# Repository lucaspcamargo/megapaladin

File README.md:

# mega-paladin v3 (WIP)

This is a switchless region mod for the SEGA Mega Drive, and a bluetooth controller host and adapter, based on the Raspberry Pi Pico W.

For now the mod is quite simple, allowing to change the region of the console via a reset button bypass.
Hold reset for half a second and release, to change desired region. The power LED will blink once for US, twice for EU, and three times for JP. Then do a quick press of the reset button to apply the setting and reset the console. Easy peasy.

Since this mod maintains the original power LED and communicates the region setting via blinking, there's no need to change anything about the external appearance of the console. It should look exactly the same after installation.

WIP WIP WIP :: Wireless controller functionality is coming along, when using a Pico W. [Bluepad32](https://github.com/ricardoquesada/bluepad32) is working well as the joystick host solution, and it supports a wide variety of controllers.

PIO for proper controller port interfacing is on the way.

For more info on this mod, and the thought process, check out TODO, and maybe also [this post](https://camargo.eng.br/blog/2023/11-18-pal-megadrive.html) for the first version.

## Building

Install dependencies for `pico-sdk`. They were `cmake gcc-arm-none-eabi libnewlib-arm-none-eabi build-essential` at time of writing (on Arch).

```
$ git submodule update --init --recursive   # pico-sdk pulls in a lot of submodules, it's ok though
$ mkdir build && cd build
$ cmake ..
$ make
```

`megapaladin.uf2` should be in the `build` folder, ready to be flashed.

## Flashing

For the first flashing, proceed as if flashing any other Pico W device via UF2. Namely:

+ use uf2 file for initial installation
+ plug usb cable in computer keeping BOOTSEL button held
+ copy uf2 file into the disk device that appears
+ umount disk

Further flashing of modified firmware after initial setup can be done with:

```sh
picotool load -f -x build/megapaladin.elf
```

`picotool` may have to be installed separately.

Use `sudo` if there are permission errors reported (most likely missing `udev` rules, if on Linux). Check the `pico-sdk` and/or the `picotool` documentation for more info.

## Hardware Installation

An installation diagram is provided [here](doc/install%20plan.png). **(It needs updating for V3!)** It is for VA 6.5, check out other switchless mod install guides for other revisions/models.

## Warnings

### Connect the USB cable only when the Mega Drive is on

The 5V supply side should be protected from reverse-feeding the console via a diode. Also, the level shifters should maintain a high-impedance state on the 5V side when the console is off.

This was tested a couple of times. I cannot guarantee this behavior, though! Weird leakage could happen, potentially damaging your console. 

You have been warned.

## License

This project is licensed under the GPL v3. See the [LICENSE](LICENSE) file for more information.

## Troubleshooting

If you encounter issues with region switching or controller connectivity, try the following steps:

- Ensure that the reset button is being properly bypassed, and that the reset button output is cut off from feeding the IO controller's reset line.
- Double-check all wiring and solder joints.
- Ensure the Pico W is properly flashed and powered.
- Verify the reset button timing as described in the usage section.
- Consult the [Bluepad32 documentation](https://github.com/ricardoquesada/bluepad32) for controller pairing issues.

## Contributing

Contributions are welcome! Please open issues or submit pull requests for bug fixes, improvements, or new features.

## Contact

For questions or feedback, [open an issue on GitHub](https://github.com/lucaspcamargo/megapaladin/issues).

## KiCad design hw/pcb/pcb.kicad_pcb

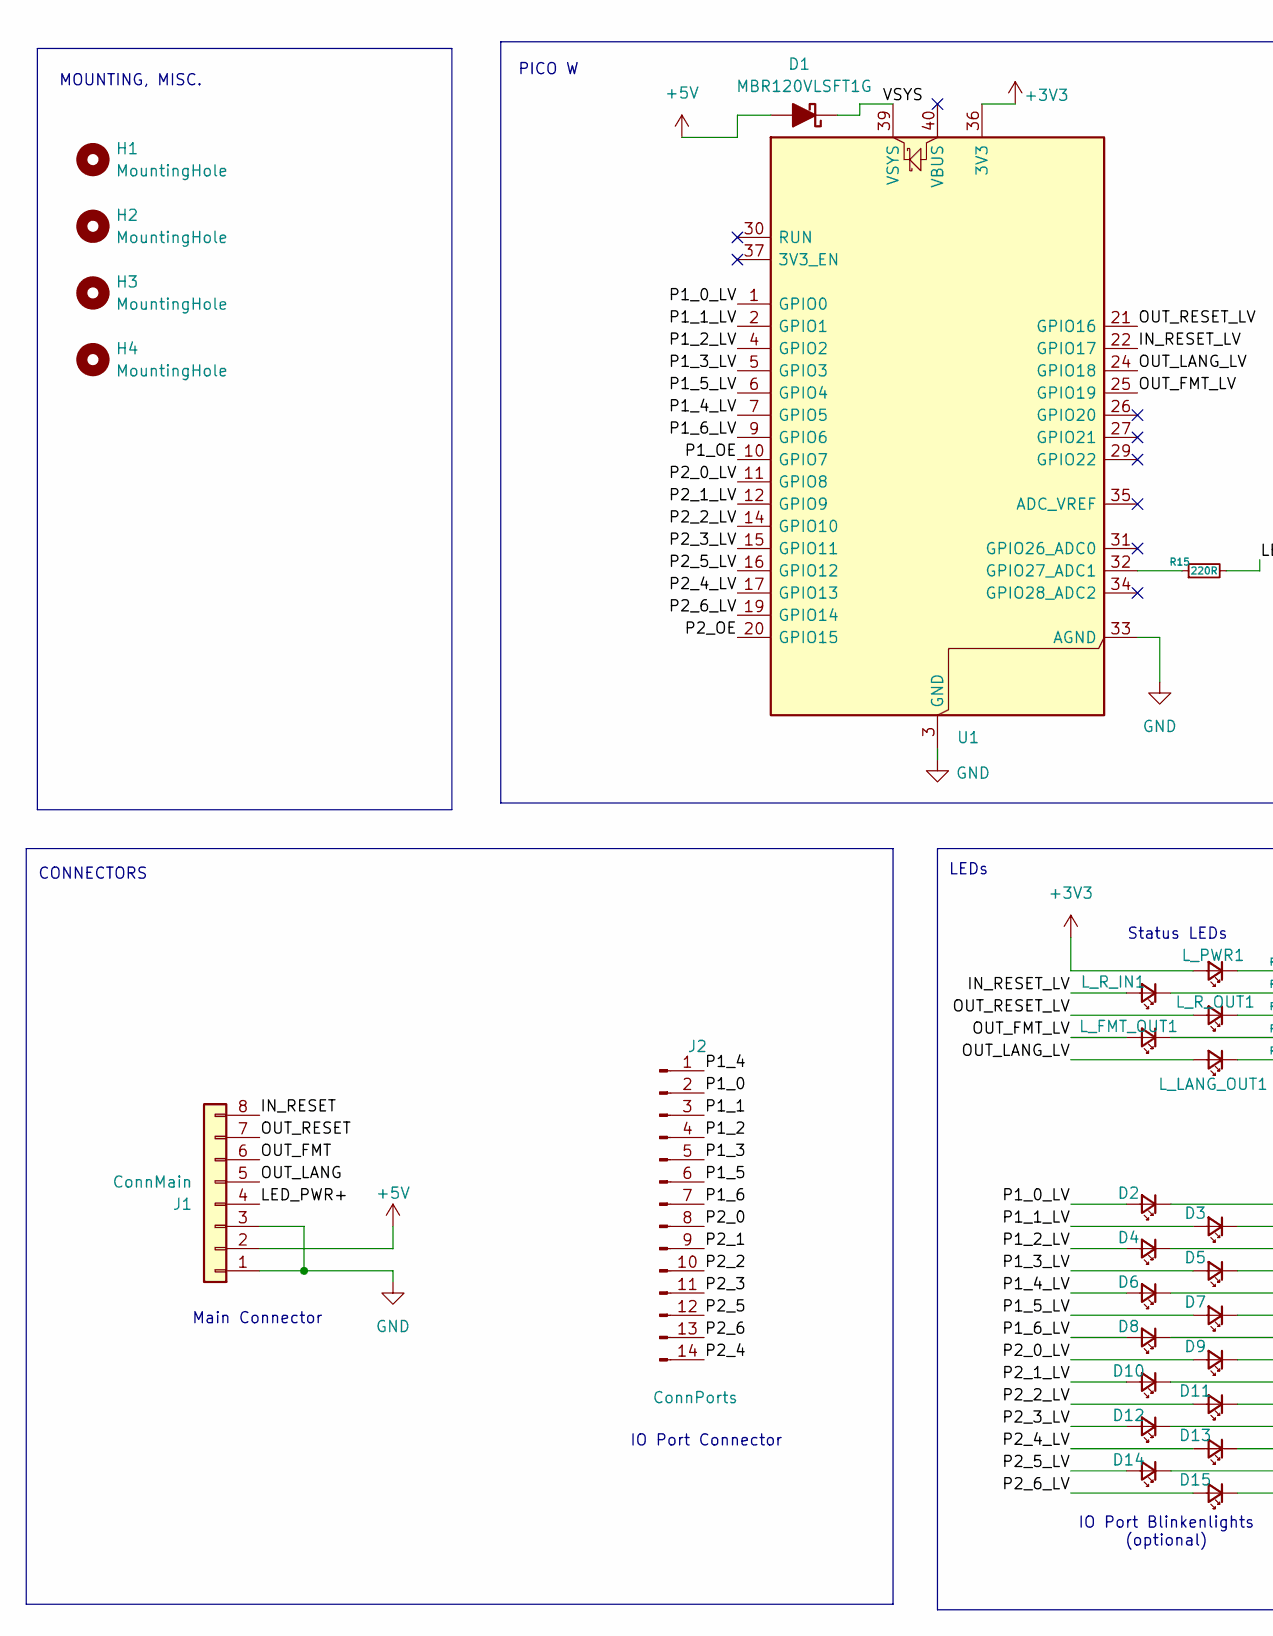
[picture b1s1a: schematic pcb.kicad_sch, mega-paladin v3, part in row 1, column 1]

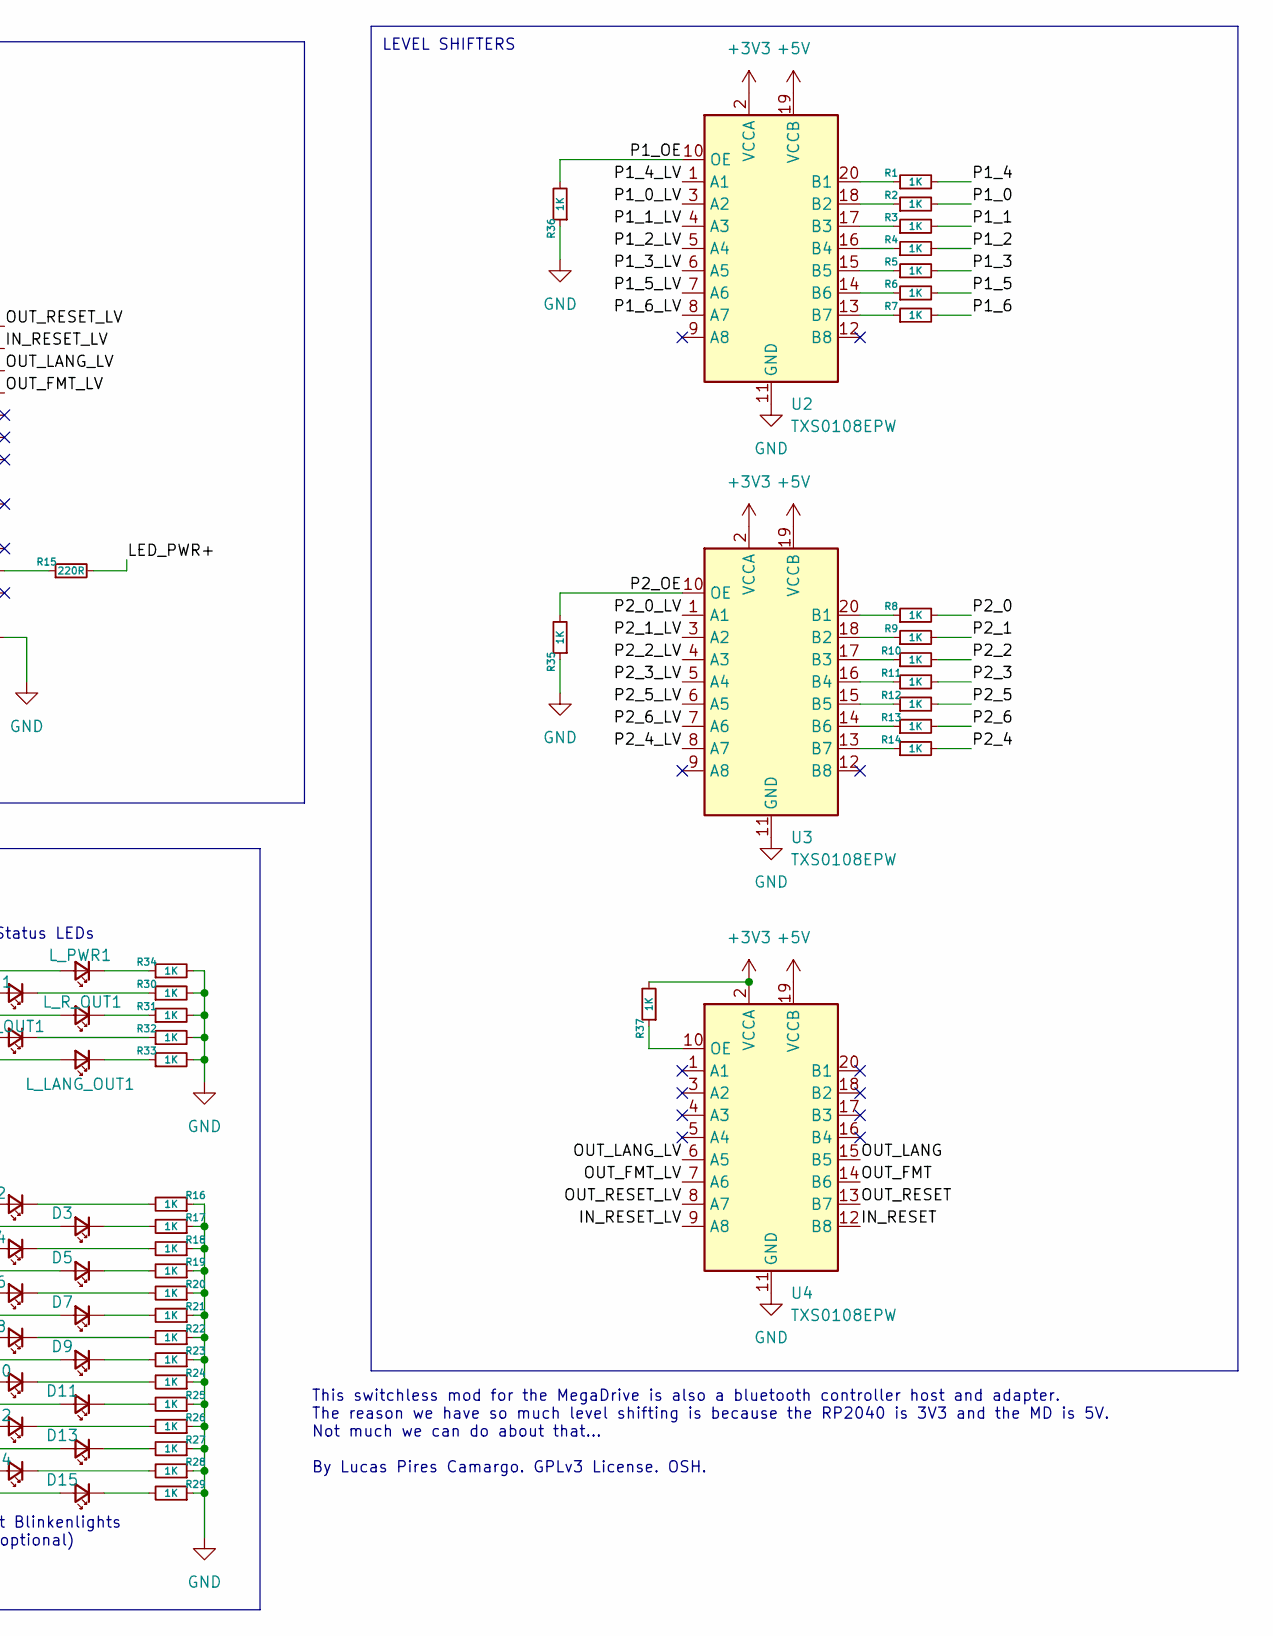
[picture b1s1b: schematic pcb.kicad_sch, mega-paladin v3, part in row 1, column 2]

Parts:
D1: MBR120VLSFT1G; D_SOD-123F; LCSC PN C223608
D2, D4, D6, D8, D10, D12, D14: LED_0805_2012Metric_Pad1.15x1.40mm_HandSolder; LCSC PN C965813
D3, D5, D7, D9, D11, D13, D15: LED_Small; LED_0805_2012Metric_Pad1.15x1.40mm_HandSolder; LCSC PN C965813
H1, H2, H3, H4: MountingHole; MountingHole_2.2mm_M2_ISO14580
J1: ConnMain; PinHeader_1x08_P2.54mm_Horizontal; LCSC PN C492416
J2: ConnPorts; PinHeader_1x14_P2.54mm_Vertical; LCSC PN C18905874
L_FMT_OUT1: LED_0805_2012Metric_Pad1.15x1.40mm_HandSolder; LCSC PN C965817
L_LANG_OUT1: LED_Small; LED_0805_2012Metric_Pad1.15x1.40mm_HandSolder; LCSC PN C965817
L_PWR1: LED_Small; LED_0805_2012Metric_Pad1.15x1.40mm_HandSolder; LCSC PN C965812
L_R_IN1: LED_0805_2012Metric_Pad1.15x1.40mm_HandSolder; LCSC PN C965817
L_R_OUT1: LED_Small; LED_0805_2012Metric_Pad1.15x1.40mm_HandSolder; LCSC PN C965817
R1, R2, R3, R4, R5, R6, R7, R8, R9, R10, R11, R12, R13, R14, R16, R17, R18, R19, R20, R21, R22, R23, R24, R25, R26, R27, R28, R29, R30, R31, R32, R33, R34, R35, R36, R37: 1K; R_0805_2012Metric_Pad1.20x1.40mm_HandSolder; LCSC PN C17513
R15: 220R; R_0805_2012Metric_Pad1.20x1.40mm_HandSolder; LCSC PN C114519
U1: RaspberryPi_Pico_W_SMD_HandSolder; LCSC PN C7203003
U2, U3, U4: TXS0108EPW; TSSOP-20_4.4x6.5mm_P0.65mm; LCSC PN C17206

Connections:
+3V3: L_PWR1.2 (A), R37.2, U1.36 (3V3), U2.2 (VCCA), U3.2 (VCCA), U4.2 (VCCA)
+5V: D1.2 (A), J1.2, U2.19 (VCCB), U3.19 (VCCB), U4.19 (VCCB)
/IN_RESET: J1.8, U4.12 (B8)
/IN_RESET_LV: L_R_IN1.2 (A), U1.22 (GPIO17), U4.9 (A8)
/LED_PWR+: J1.4, R15.2
/OUT_FMT: J1.6, U4.14 (B6)
/OUT_FMT_LV: L_FMT_OUT1.2 (A), U1.25 (GPIO19), U4.7 (A6)
/OUT_LANG: J1.5, U4.15 (B5)
/OUT_LANG_LV: L_LANG_OUT1.2 (A), U1.24 (GPIO18), U4.6 (A5)
/OUT_RESET: J1.7, U4.13 (B7)
/OUT_RESET_LV: L_R_OUT1.2 (A), U1.21 (GPIO16), U4.8 (A7)
/P1_0: J2.2, R2.2
/P1_0_LV: D2.2 (A), U1.1 (GPIO0), U2.3 (A2)
/P1_1: J2.3, R3.2
/P1_1_LV: D3.2 (A), U1.2 (GPIO1), U2.4 (A3)
/P1_2: J2.4, R4.2
/P1_2_LV: D4.2 (A), U1.4 (GPIO2), U2.5 (A4)
/P1_3: J2.5, R5.2
/P1_3_LV: D5.2 (A), U1.5 (GPIO3), U2.6 (A5)
/P1_4: J2.1, R1.2
/P1_4_LV: D6.2 (A), U1.7 (GPIO5), U2.1 (A1)
/P1_5: J2.6, R6.2
/P1_5_LV: D7.2 (A), U1.6 (GPIO4), U2.7 (A6)
/P1_6: J2.7, R7.2
/P1_6_LV: D8.2 (A), U1.9 (GPIO6), U2.8 (A7)
/P1_OE: R36.2, U1.10 (GPIO7), U2.10 (OE)
/P2_0: J2.8, R8.2
/P2_0_LV: D9.2 (A), U1.11 (GPIO8), U3.1 (A1)
/P2_1: J2.9, R9.2
/P2_1_LV: D10.2 (A), U1.12 (GPIO9), U3.3 (A2)
/P2_2: J2.10, R10.2
/P2_2_LV: D11.2 (A), U1.14 (GPIO10), U3.4 (A3)
/P2_3: J2.11, R11.2
/P2_3_LV: D12.2 (A), U1.15 (GPIO11), U3.5 (A4)
/P2_4: J2.14, R14.2
/P2_4_LV: D13.2 (A), U1.17 (GPIO13), U3.8 (A7)
/P2_5: J2.12, R12.2
/P2_5_LV: D14.2 (A), U1.16 (GPIO12), U3.6 (A5)
/P2_6: J2.13, R13.2
/P2_6_LV: D15.2 (A), U1.19 (GPIO14), U3.7 (A6)
/P2_OE: R35.2, U1.20 (GPIO15), U3.10 (OE)
/VSYS: D1.1 (K), U1.39 (VSYS)
GND: J1.1, J1.3, R16.1, R17.1, R18.1, R19.1, R20.1, R21.1, R22.1, R23.1, R24.1, R25.1, R26.1, R27.1, R28.1, R29.1, R30.2, R31.2, R32.2, R33.2, R34.2, R35.1, R36.1, U1.3 (GND), U1.8 (GND), U1.13 (GND), U1.18 (GND), U1.23 (GND), U1.28 (GND), U1.33 (AGND), U1.38 (GND), U2.11 (GND), U3.11 (GND), U4.11 (GND)
unnamed: D2.1 (K), R16.2
unnamed: D3.1 (K), R17.2
unnamed: D4.1 (K), R18.2
unnamed: D5.1 (K), R19.2
unnamed: D6.1 (K), R20.2
unnamed: D7.1 (K), R21.2
unnamed: D8.1 (K), R22.2
unnamed: D9.1 (K), R23.2
unnamed: D10.1 (K), R24.2
unnamed: D11.1 (K), R25.2
unnamed: D12.1 (K), R26.2
unnamed: D13.1 (K), R27.2
unnamed: D14.1 (K), R28.2
unnamed: D15.1 (K), R29.2
unnamed: L_FMT_OUT1.1 (K), R32.1
unnamed: L_LANG_OUT1.1 (K), R33.1
unnamed: L_PWR1.1 (K), R34.1
unnamed: L_R_IN1.1 (K), R30.1
unnamed: L_R_OUT1.1 (K), R31.1
unnamed: R15.1, U1.32 (GPIO27_ADC1)
unnamed: R1.1, U2.20 (B1)
unnamed: R2.1, U2.18 (B2)
unnamed: R3.1, U2.17 (B3)
unnamed: R4.1, U2.16 (B4)
unnamed: R5.1, U2.15 (B5)
unnamed: R6.1, U2.14 (B6)
unnamed: R7.1, U2.13 (B7)
unnamed: R8.1, U3.20 (B1)
unnamed: R9.1, U3.18 (B2)
unnamed: R10.1, U3.17 (B3)
unnamed: R11.1, U3.16 (B4)
unnamed: R12.1, U3.15 (B5)
unnamed: R13.1, U3.14 (B6)
unnamed: R14.1, U3.13 (B7)
unnamed: R37.1, U4.10 (OE)

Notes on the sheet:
Main Connector
MOUNTING, MISC.
LEDs
IO Port Blinkenlights (optional)
Status LEDs
LEVEL SHIFTERS
PICO W
This switchless mod for the MegaDrive is also a bluetooth controller host and adapter. The reason we have so much level shifting is because the RP2040 is 3V3 and the MD is 5V. Not much we can do about that... By Lucas Pires Camargo. GPLv3 License. OSH.
CONNECTORS
IO Port Connector

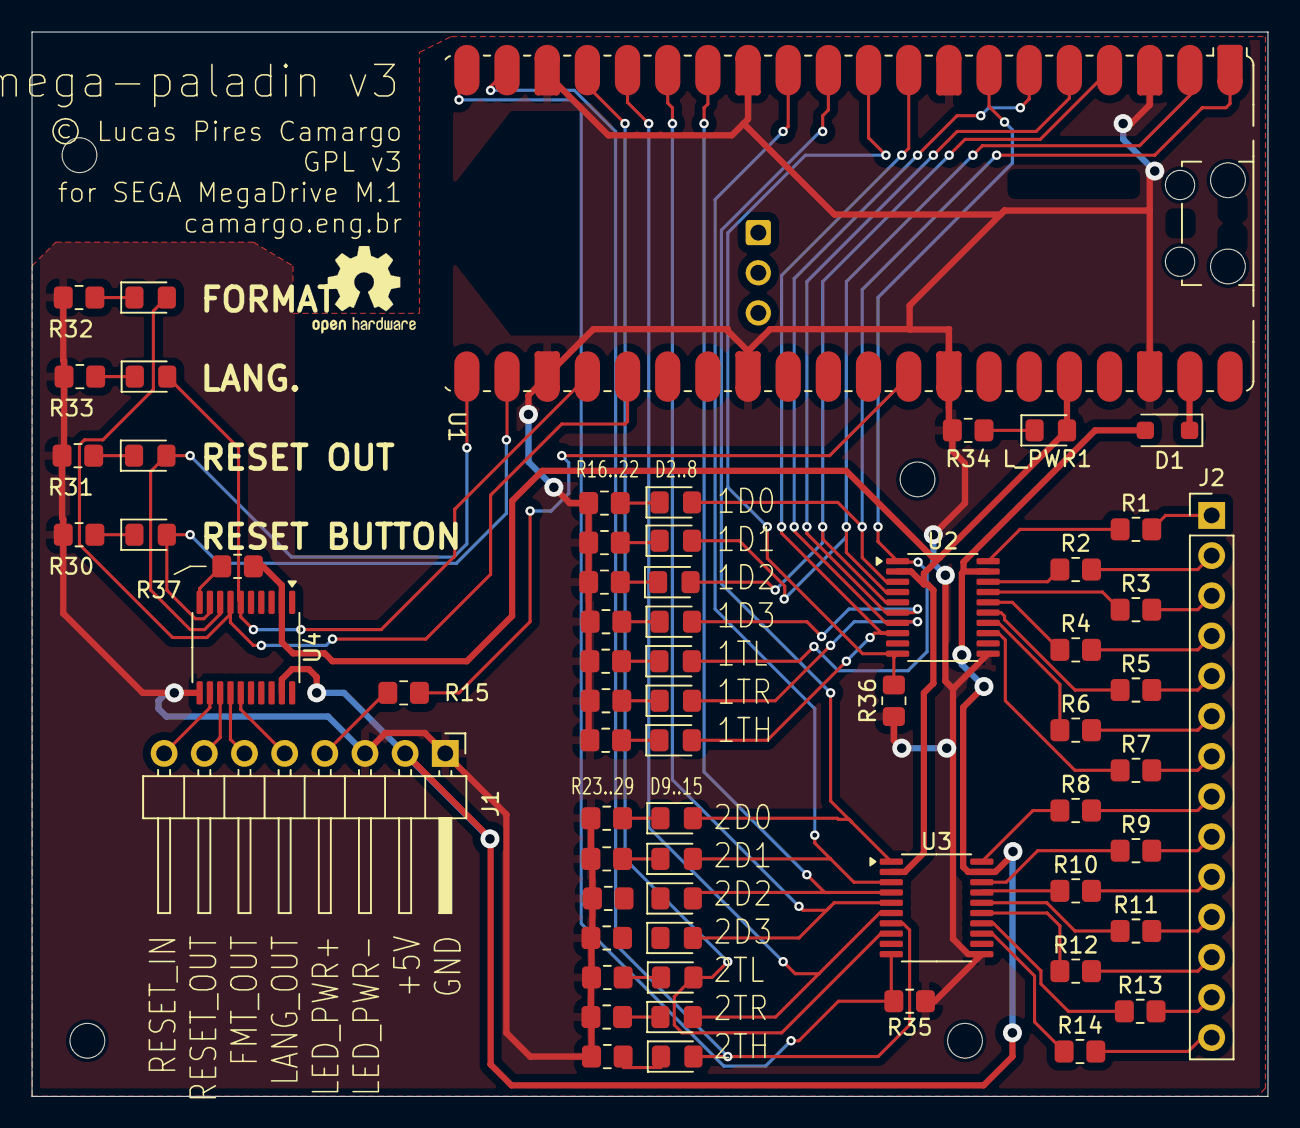
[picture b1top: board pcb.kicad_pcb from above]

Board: 2 copper layers, 78.2 x 67.3 mm, 67 parts (0 on the bottom side), 78 nets.

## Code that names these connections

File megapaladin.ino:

#include <Arduino.h>

enum Region
{
  REGION_US,
  REGION_EU,
  REGION_JP,
  REGION_COUNT
};

enum Format
{
  FMT_NTSC = 0,
  FMT_PAL = 1
};

enum Language
{
  LANG_JP = 0,
  LANG_EN = 1  
};

const uint8_t mapping[][2] = {
  {LANG_EN, FMT_NTSC},  // REGION_US
  {LANG_EN, FMT_PAL},  // REGION_EU
  {LANG_JP, FMT_NTSC}   // REGION_JP
};

#define PIN_IN_RESET 18
#define PIN_OUT_RESET 19
#define PIN_OUT_FMT 20
#define PIN_OUT_LANG 21
#define PIN_OUT_PWR_LED 22

Region curr_region = REGION_US;


void setRegionOutputs();

void setup() {
  pinMode(PIN_IN_RESET, INPUT_PULLUP);
  pinMode(PIN_OUT_RESET, OUTPUT);
  pinMode(PIN_OUT_FMT, OUTPUT);
  pinMode(PIN_OUT_LANG, OUTPUT);
  pinMode(PIN_OUT_PWR_LED, OUTPUT);

  setRegionOutputs();

}

void loop() {
  
}

void setRegionOutputs()
{
  digitalWrite(PIN_OUT_LANG, mapping[curr_region][0]);
  digitalWrite(PIN_OUT_FMT, mapping[curr_region][1]);
}

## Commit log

2023-11-17 added install drawing
2023-11-18 added firmware skeleton
2023-11-18 added arduino sketch for arduino-pico
2023-11-18 first working version (simple switchless)\nstopped using platformio for now, using simple arduino-pico sketch
2023-11-18 added readme and updated install diagram
2023-11-18 install plan in png to avoid svg rendering issue
2023-11-18 install plan export settings
2023-11-19 OTA wifi and preparation for bluetooth
2023-11-20 added license
2023-11-21 halfway porting to pico-sdk and away from arduino-pico
2023-11-21 pico-sdk port progress
2023-11-22 added planned pinout for controller ports
2023-11-22 compiling under pico sdk
2023-11-22 port progress
2023-11-22 added bluepad32 submodule
2023-11-22 linking with bluepad32
2023-11-23 moved some things around
2023-11-23 added multicore flash concurrency init, this fixed the crashes. cyw43 and core 1 coexist now
2023-11-23 readded mem info code, used newlib api reference
2023-11-28 basic functionality reinstated, pico-sdk port of v1 is done
2023-12-11 using queue, console restored, sync hold working
2023-12-11 fixed button debounce on release, led behavior, updated TODO
2023-12-11 updated bluepad32
2024-04-01 updated bluepad32 version and made necessary changes, added old v1 version just in case
2024-05-04 updated dep versions, bt_platform progress
2024-05-06 port api draft, general progress handling events
2024-05-13 impl: controller data packing, install diagram update
2024-05-17 added pcb project, updated readme
2024-06-30 general progress
2024-08-05 changed to use gpio irqs for fast response in port code, general changes
2025-05-25 adding leftover changes in preparation for v3
2025-06-14 [hw] initial v3 design, updated readme
2025-06-15 [hw] final tweaks for pcb, incl. fabrication files
2025-06-16 [hw] added note to schematic about TL and TR order
2025-07-08 [defs,doc] changed pin assignments to match v3 hw
2025-07-12 [general] misc fixes and preparation for v3
2025-07-12 [readme] cleanup
2025-07-12 [general] updated TODO, pico-sdk version
2025-07-12 [readme] more cleanup
2025-07-13 trying out pio, sniffer progress
2025-07-13 pio handling fixes
2025-07-14 [fw] pio init fixes
2025-07-27 [cmake,subm] added EmbeddedCLI dependency

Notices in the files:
hw/pcb/pcb.kicad_pcb:
© Lucas Pires Camargo
GPL v3
